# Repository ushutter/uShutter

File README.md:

# uShutter

Introduction video on Youtube:

uShutter is an open, reproducible shutter timing specification and implementation, focused on time-domain shutter speed and curtain travel measurement.

uShutter provides a firmware and multiple reference hardware interface implementation for measuring:
* shutter exposure time and stability
* curtain travel time and stability

It uses pure time-domain signals from different optical sensors. Measurement accuracy highly depends on the sensors selected and PCB board manufacturing quality.

## What uShutter Is
* An open measurement core for shutter timing
* A reference implementation for single- and dual-sensor setups
* A stable timing interface others can implement or extend
* Suitable for DIY, education, analysis, and experimentation

## Core Capabilities (Open Scope)
uShutter includes the following open-source capabilities:
### Shutter Timing
* Optical trigger–based event capture
* Microsecond-resolution timestamps
* Direction-independent logic
### Single-Sensor Measurement
* Exposure duration measurement
* Multi-shot repeatability analysis
### Dual-Sensor Curtain Analysis
* Curtain travel time
* Relative curtain speed

## Hardware Philosophy
uShutter is designed to work with:
* Arduino / ATmega328P MCUs
* Simple optical sensors (e.g. LM393-based comparators)
* No specific sensor type, threshold method, or light source is assumed by the interface.

## Project Structure
/Firmware    Code implementation 

/Hardware    Reference schematics and layouts

[Theory, usage, and build notes](https://ushutter90.wordpress.com/how-to/)

## License
Firmware: Apache License 2.0

Hardware designs: CERN-OHL-S

This project is open by design and intent.

## Status
uShutter is under active development.

Interface stability and clarity take priority over feature expansion.

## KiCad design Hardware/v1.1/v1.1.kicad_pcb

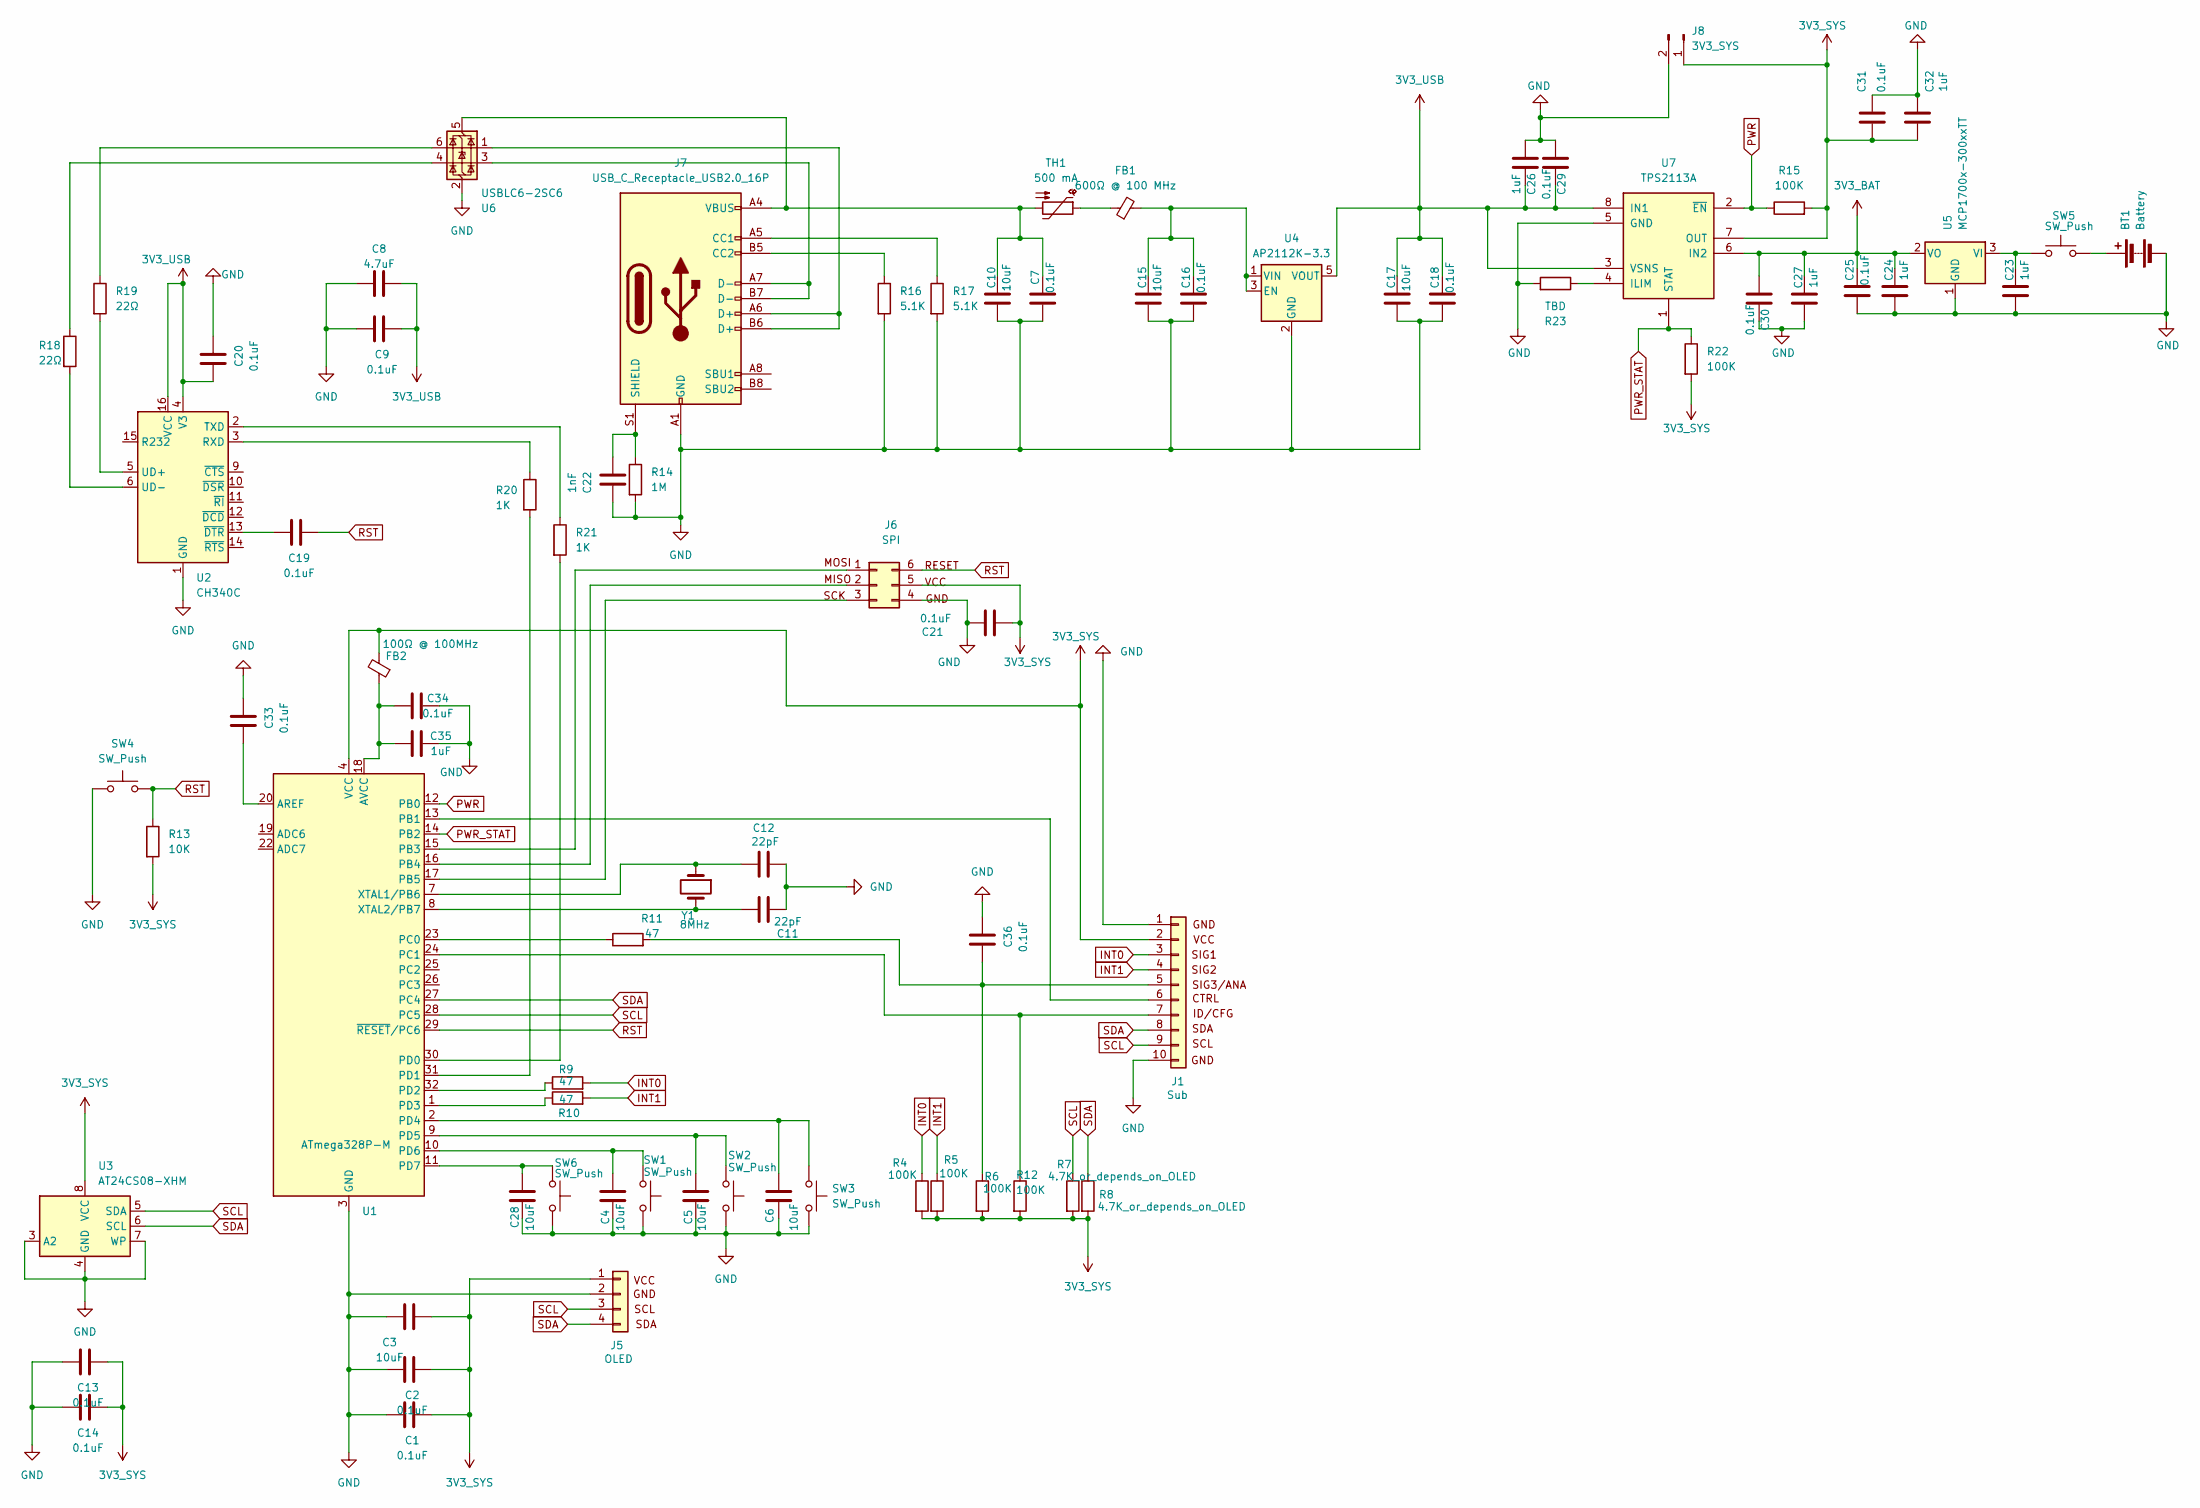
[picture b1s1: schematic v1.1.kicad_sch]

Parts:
BT1: Battery; PinHeader_1x02_P2.54mm_Vertical
C1, C2, C7, C9, C13, C14, C16, C18, C19, C20, C21, C25, C29, C30, C31, C33, C34, C36: 0.1uF; C_0603_1608Metric
C3, C4, C5, C6, C10, C15, C17, C28: 10uF; C_0805_2012Metric
C8: 4.7uF; C_0603_1608Metric
C11, C12: 22pF; C_0603_1608Metric
C22: 1nF; C_0603_1608Metric
C23, C24, C26, C27, C32, C35: 1uF; C_0603_1608Metric
FB1: 600Ω @ 100 MHz; L_0603_1608Metric
FB2: 100Ω @ 100MHz; L_0603_1608Metric
J1: Sub; PinSocket_2x05_P2.54mm_Vertical
J5: OLED; PinSocket_1x04_P2.54mm_Vertical
J6: SPI; PinSocket_2x03_P2.54mm_Vertical
J7: USB_C_Receptacle_USB2.0_16P; USB_C_Receptacle_Palconn_UTC16-G
J8: 3V3_SYS; PinHeader_1x02_P2.54mm_Vertical
R4, R5, R6, R12, R15, R22: 100K; R_0603_1608Metric
R7, R8: 4.7K_or_depends_on_OLED; R_0603_1608Metric
R9, R10, R11: 47; R_0603_1608Metric
R13: 10K; R_0603_1608Metric
R14: 1M; R_0603_1608Metric
R16, R17: 5.1K; R_0603_1608Metric
R18, R19: 22Ω; R_0603_1608Metric
R20, R21: 1K; R_0603_1608Metric
R23: TBD; R_0603_1608Metric
SW1, SW2, SW3, SW6: SW_Push; SW_PUSH_6mm
SW4, SW5: SW_Push; PinHeader_1x02_P2.54mm_Vertical
TH1: 500 mA; Fuse_1206_3216Metric
U1: ATmega328P-M; TQFP-32_7x7mm_P0.8mm
U2: CH340C; SOP-16_4.4x10.4mm_P1.27mm
U3: AT24CS08-XHM; TSSOP-8_4.4x3mm_P0.65mm
U4: AP2112K-3.3; SOT-23-5
U5: MCP1700x-300xxTT; SOT-23
U6: USBLC6-2SC6; SOT-23-6
U7: TPS2113A; TSSOP-8_4.4x3mm_P0.65mm
Y1: 8MHz; Crystal_SMD_5032-2Pin_5.0x3.2mm

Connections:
3V3_BAT: C24.2, C25.2, C27.2, C30.1, U5.2 (VO), U7.6 (IN2)
3V3_SYS: C1.2, C2.2, C3.2, C13.2, C14.2, C21.1, C31.2, C32.1, FB2.2, J1.2, J5.1, J6.5, J8.1, R4.2, R5.2, R6.2, R7.2, R8.2, R12.2, R13.2, R15.2, R22.2, U1.4 (VCC), U1.6 (VCC), U3.8 (VCC), U7.7 (OUT)
3V3_USB: C8.2, C9.2, C17.2, C18.2, C20.1, C26.2, C29.2, U2.4 (V3), U2.16 (VCC), U4.5 (VOUT), U7.3 (VSNS), U7.8 (IN1)
GND: BT1.2 (-), C1.1, C2.1, C3.1, C4.2, C5.2, C6.2, C7.1, C8.1, C9.1, C10.1, C11.2, C12.2, C13.1, C14.1, C15.1, C16.1, C17.1, C18.1, C20.2, C21.2, C22.2, C23.1, C24.1, C25.1, C26.1, C27.1, C28.2, C29.1, C30.2, C31.1, C32.2, C33.2, C34.2, C35.2, C36.2, J1.1, J1.10, J5.2, J6.4, J7.A1 (GND), J7.A12 (GND), J7.B1 (GND), J7.B12 (GND), J8.2, R14.2, R16.2, R17.2, R23.2, SW1.2, SW2.2, SW3.2, SW4.1, SW6.2, U1.3 (GND), U1.5 (GND), U1.21 (GND), U1.33 (GND), U2.1 (GND), U3.3 (A2), U3.4 (GND), U3.7 (WP), U4.2 (GND), U5.1 (GND), U6.2 (GND), U7.5 (GND)
INT0: J1.3, R4.1, R9.2
INT1: J1.4, R5.1, R10.2
unnamed: BT1.1 (+), SW5.2
unnamed: FB1.1, TH1.1
unnamed: C36.1, J1.5, R6.1, R11.2
unnamed: J1.6, U1.13 (PB1)
unnamed: J1.7, R12.1, U1.24 (PC1)
unnamed: J6.1, U1.15 (PB3)
unnamed: J6.2, U1.16 (PB4)
unnamed: J6.3, U1.17 (PB5)
unnamed: J7.A5 (CC1), R17.1
unnamed: J7.B5 (CC2), R16.1
unnamed: J7.A6 (D+), J7.B6 (D+), U6.1 (I/O1)
unnamed: J7.A7 (D-), J7.B7 (D-), U6.3 (I/O2)
unnamed: C22.1, J7.S1 (SHIELD), R14.1
unnamed: R18.1, U6.4 (I/O2)
unnamed: R19.1, U6.6 (I/O1)
unnamed: C33.1, U1.20 (AREF)
unnamed: C34.1, C35.1, FB2.1, U1.18 (AVCC)
unnamed: R11.1, U1.23 (PC0)
unnamed: R21.2, U1.30 (PD0)
unnamed: R20.2, U1.31 (PD1)
unnamed: R9.1, U1.32 (PD2)
unnamed: R10.1, U1.1 (PD3)
unnamed: C6.1, SW3.1, U1.2 (PD4)
unnamed: C5.1, SW2.1, U1.9 (PD5)
unnamed: C4.1, SW1.1, U1.10 (PD6)
unnamed: C28.1, SW6.1, U1.11 (PD7)
unnamed: C12.1, U1.7 (XTAL1/PB6), Y1.1
unnamed: C11.1, U1.8 (XTAL2/PB7), Y1.2
unnamed: R20.1, U2.3 (RXD)
unnamed: R21.1, U2.2 (TXD)
unnamed: R19.2, U2.5 (UD+)
unnamed: R18.2, U2.6 (UD-)
unnamed: C19.1, U2.13 (~DTR)
unnamed: C15.2, C16.2, FB1.2, U4.1 (VIN), U4.3 (EN)
unnamed: C23.2, SW5.1, U5.3 (VI)
unnamed: C7.2, C10.2, J7.A4 (VBUS), J7.A9 (VBUS), J7.B4 (VBUS), J7.B9 (VBUS), TH1.2, U6.5 (VBUS)
unnamed: R23.1, U7.4 (ILIM)
PWR: R15.1, U1.12 (PB0), U7.2 (~EN)
PWR_STAT: R22.1, U1.14 (PB2), U7.1 (STAT)
RST: C19.2, J6.6, R13.1, SW4.2, U1.29 (~RESET/PC6)
SCL: J1.9, J5.3, R7.1, U1.28 (PC5), U3.5 (SDA)
SDA: J1.8, J5.4, R8.1, U1.27 (PC4), U3.6 (SCL)

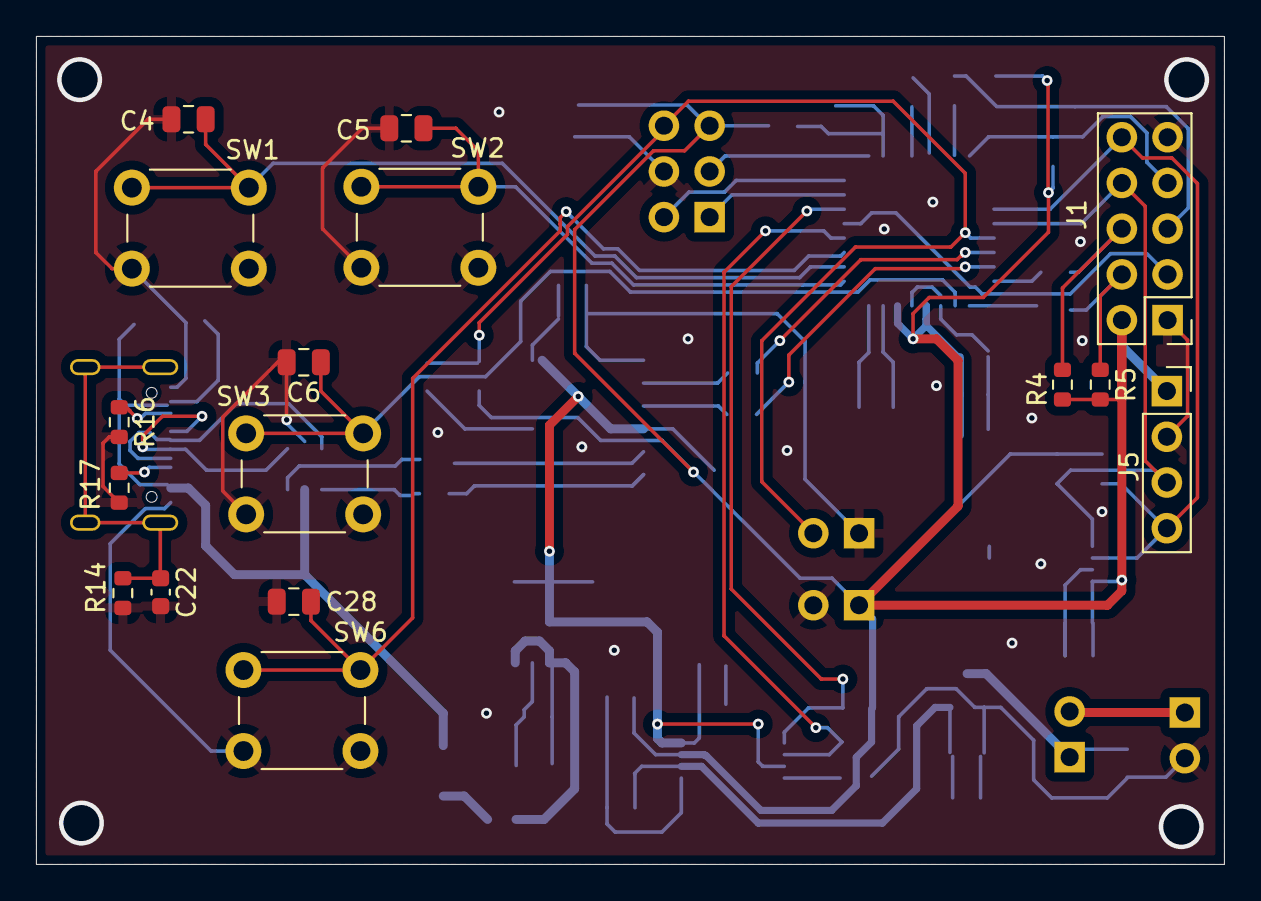
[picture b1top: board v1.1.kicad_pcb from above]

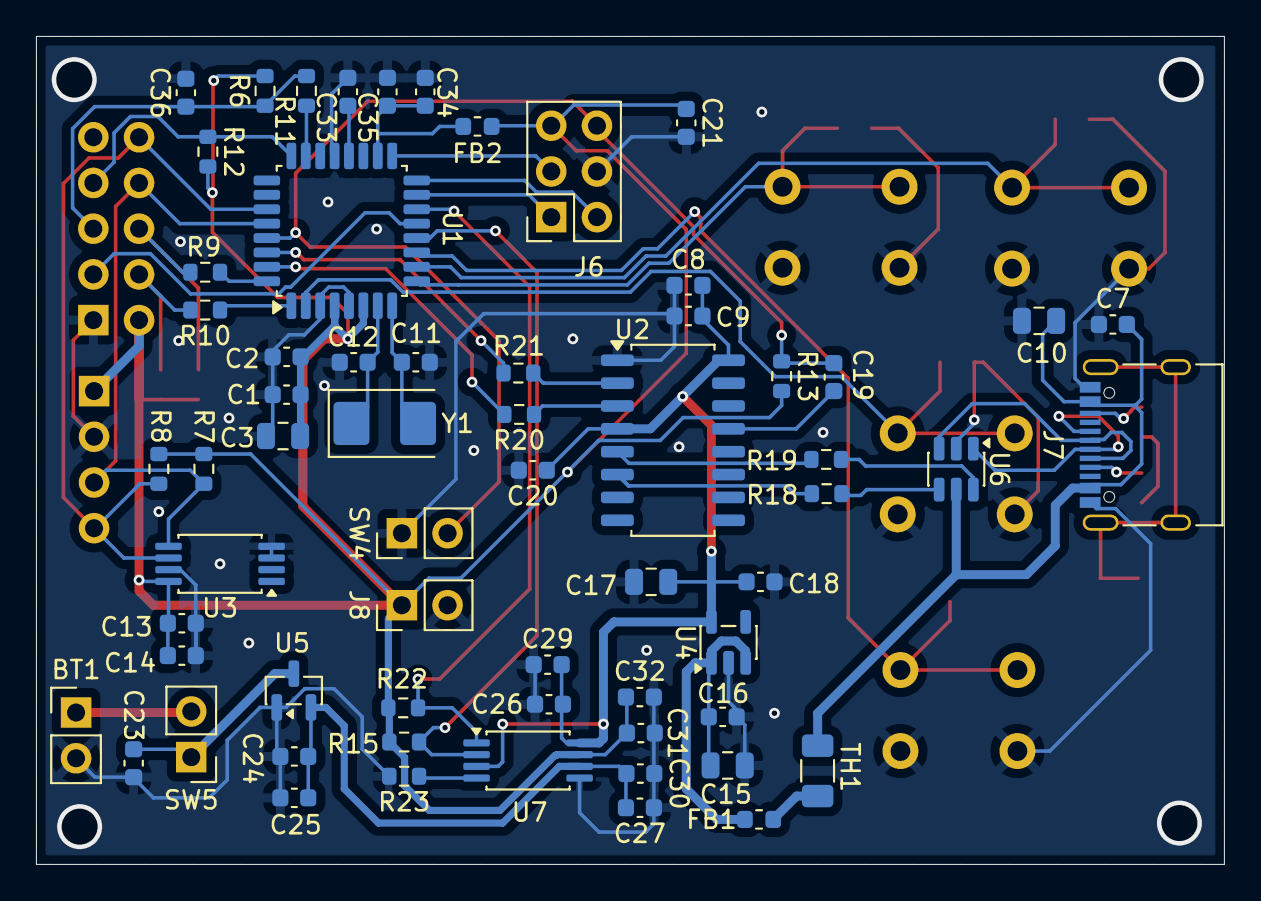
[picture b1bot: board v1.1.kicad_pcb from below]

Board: 2 copper layers, 66.0 x 46.0 mm, 79 parts (63 on the bottom side), 48 nets.

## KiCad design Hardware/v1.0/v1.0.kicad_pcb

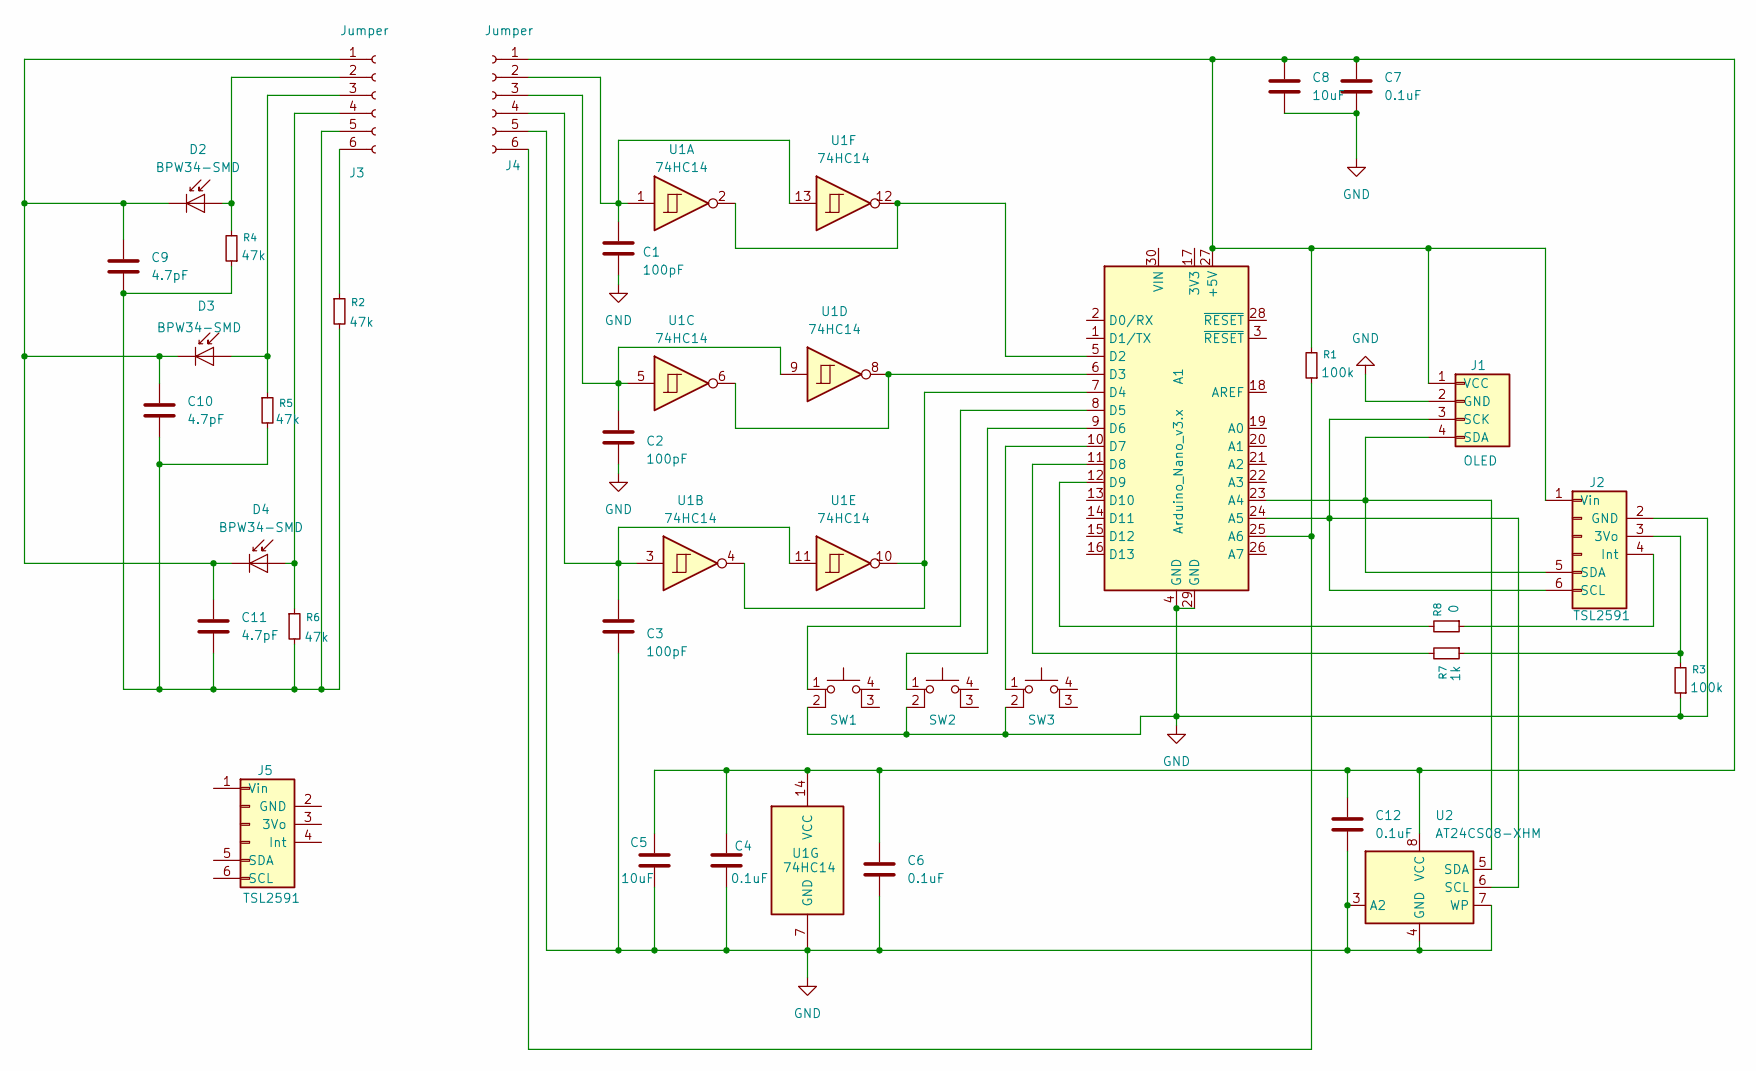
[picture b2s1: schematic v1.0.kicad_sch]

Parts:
A1: Arduino_Nano_v3.x; Arduino_Nano
C1, C2, C3: 100pF; C_0603_1608Metric
C4, C6, C7, C12: 0.1uF; C_0603_1608Metric
C5, C8: 10uF; C_0603_1608Metric
C9, C10, C11: 4.7pF; C_0603_1608Metric
D2, D3, D4: BPW34-SMD; Osram_BPW34S-SMD
J1: OLED; R_Array_SIP4
J2, J5: TSL2591; R_Array_SIP6
J3, J4: Jumper; R_Array_SIP6
R1, R3: 100k; R_0603_1608Metric
R2, R4, R5, R6: 47k; R_0603_1608Metric
R7: 1k; R_0603_1608Metric
R8: 0; R_0603_1608Metric
SW1, SW2, SW3: SW_MEC_5E; SW_PUSH_6mm
U1: 74HC14; SSOP-14_5.3x6.2mm_P0.65mm
U2: AT24CS08-XHM; TSSOP-8_4.4x3mm_P0.65mm

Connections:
GND: A1.4 (GND), A1.29 (GND), C1.2, C2.2, C3.2, C4.2, C5.2, C6.2, C7.2, C8.2, C12.2, J1.2 (GND), J2.2 (GND), J4.5, R3.1, SW1.2, SW2.2, SW3.2, U1.7 (GND), U2.3 (A2), U2.4 (GND), U2.7 (WP)
unnamed: A1.27 (+5V), C4.1, C5.1, C6.1, C7.1, C8.1, C12.1, J1.1 (VCC), J2.1 (Vin), J4.1, R1.2, U1.14 (VCC), U2.8 (VCC)
unnamed: A1.23 (A4), J1.4 (SDA), J2.5 (SDA), U2.5 (SDA)
unnamed: A1.24 (A5), J1.3 (SCK), J2.6 (SCL), U2.6 (SCL)
unnamed: A1.25 (A6), J4.6, R1.1
unnamed: A1.5 (D2), U1.2, U1.12
unnamed: A1.6 (D3), U1.6, U1.8
unnamed: A1.7 (D4), U1.4, U1.10
unnamed: A1.8 (D5), SW1.1
unnamed: A1.9 (D6), SW2.1
unnamed: A1.10 (D7), SW3.1
unnamed: A1.11 (D8), R7.2
unnamed: A1.12 (D9), R8.2
unnamed: D2.2 (A), J3.2, R4.2
unnamed: C9.1, C10.1, C11.1, D2.1 (K), D3.1 (K), D4.1 (K), J3.1
unnamed: D3.2 (A), J3.3, R5.1
unnamed: D4.2 (A), J3.4, R6.1
unnamed: J2.3 (3Vo), R3.2, R7.1
unnamed: J2.4 (Int), R8.1
unnamed: C9.2, C10.2, C11.2, J3.5, R2.2, R4.1, R5.2, R6.2
unnamed: J3.6, R2.1
unnamed: C1.1, J4.2, U1.1, U1.13
unnamed: C2.1, J4.3, U1.5, U1.9
unnamed: C3.1, J4.4, U1.3, U1.11

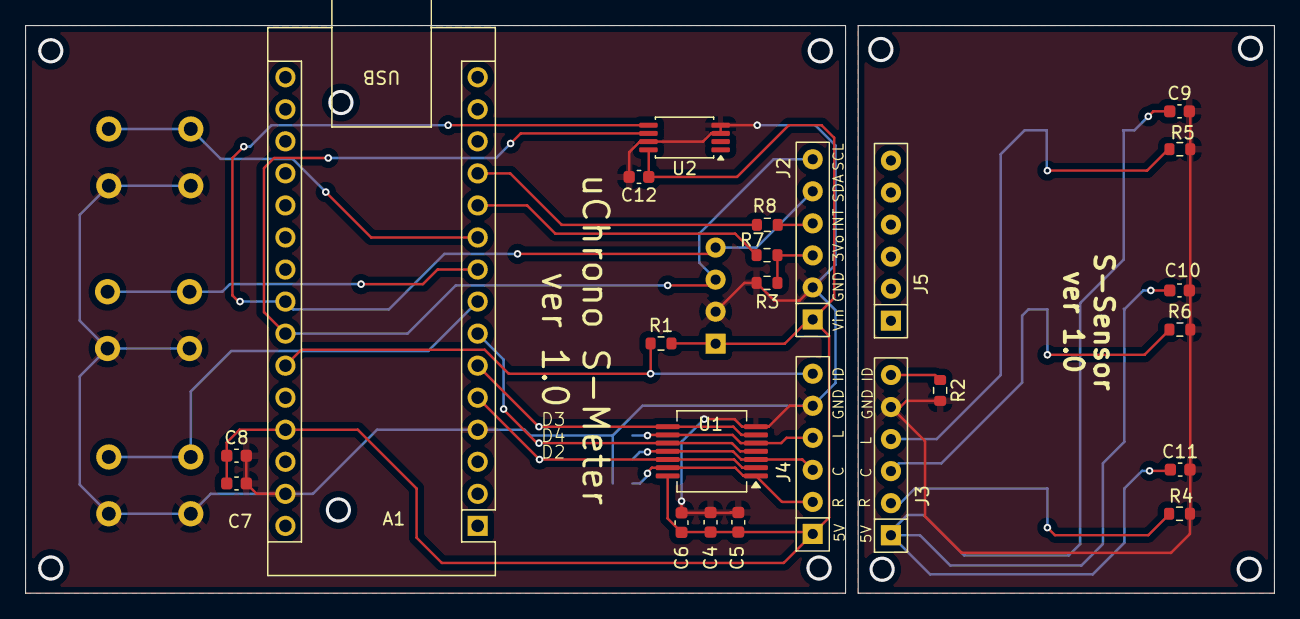
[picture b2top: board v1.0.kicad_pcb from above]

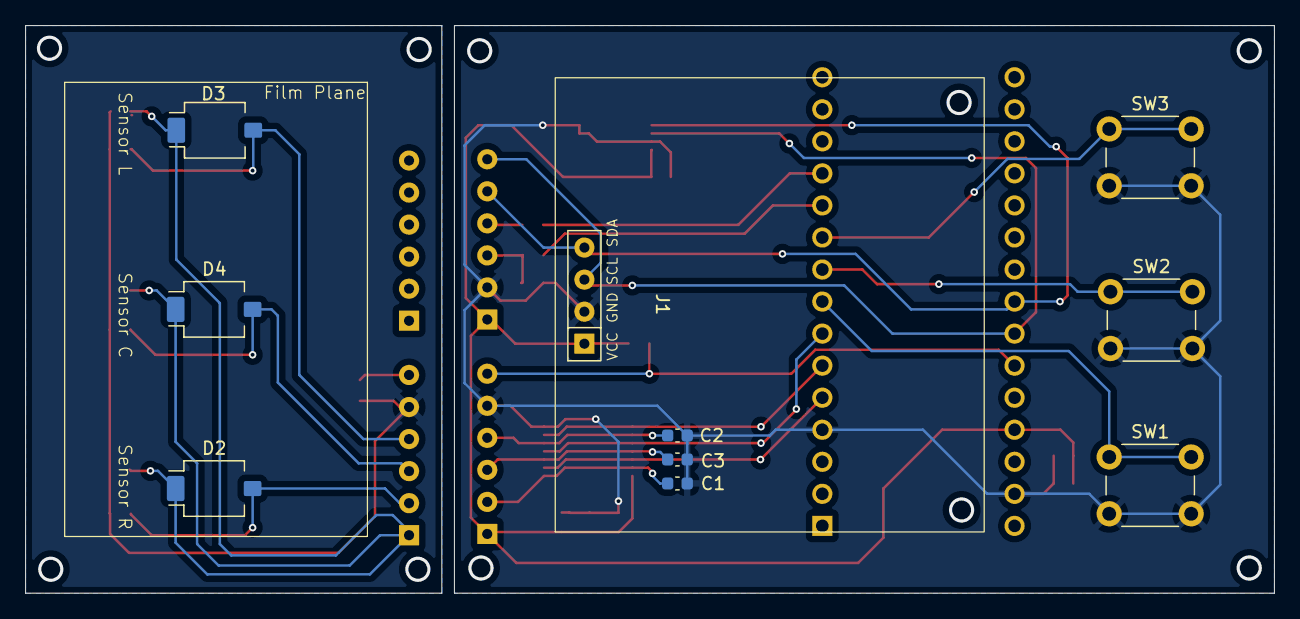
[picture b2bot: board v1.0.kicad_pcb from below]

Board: 2 copper layers, 99.0 x 45.0 mm, 34 parts (10 on the bottom side), 24 nets.

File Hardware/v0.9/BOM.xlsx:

Id | 类型 | 型号 | 封装 |  | 数量
1 | U1 | 74HC14 SSOP | SSOP-14_5.3x6.2mm_P0.65mm | 1 | 6
2 | U2 | AT24CS16-XHM TSSOP | TSSOP-8_4.4x3mm_P0.65mm | 1 | 6
3 | D2,D3,D4 | VISHAY_BPW34S | SMD | 3 | 18
4 | SW3,SW1,SW2 | 开关 | SW_PUSH_6mm | 3 | 18
5 | J1 | 1x4孔排针插座2.54mm | SIP4 | 1 | 6
6 | J3 | 1x6孔90度排针2.54mm | SIP6 | 2 | 12
7 | J2,J5 | 1x6孔排针插座2.54mm | SIP6 | 2 | 12
8 | J4 | 1x10孔排针插座2.54mm | SIP10 | 2 | 12
9 | R3,R1 | 100k | R_0603_1608Metric | 2 | 40
10 | R5,R2,R6,R4 | 47k | R_0603_1608Metric | 4 | 80
11 | R7 | 1k | R_0603_1608Metric | 1 | 20
12 | C3,C1,C2 | 100pF | C_0603_1608Metric | 3 | 60
13 | C5,C8 | 10uF | C_0603_1608Metric | 2 | 40
14 | C4,C12,C7,C6 | 0.1uF | C_0603_1608Metric | 4 | 80
15 | C11,C9,C10 | 4.7pF | C_0603_1608Metric | 3 | 60
16 | PCB安装螺丝 |  | 2mm | 10 | 50
17 | 其他电阻电容 |  | C_0603_1608Metric |  | 若干

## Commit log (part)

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2026-02-05 init
2026-02-05 remove hardware
2026-02-05 Format README.md with Markdown syntax
2026-02-05 setup
2026-02-05 update HW
2026-02-05 update readme and license
2026-02-05 Fix README formatting and update links
    Corrected capitalization and updated documentation links.
2026-02-08 release v0.9.2
2026-02-26 update code according to v1.0.3 hardware, functionalies are equivalent to v0.9.2 code. 1. Add 74AHC14 display 2. adjust ID/CFG resistor and adc value, 3. allow user to select sensor for single mode
2026-02-26 add all
2026-02-26 Revert "add all"
    This reverts commit acbe82ba5c7bee5f6fd0c139b5e62855f1dc90a6.
2026-02-26 latest
2026-03-08 Move uShutter sketch from Firmware/v0.9.4 to Firmware root
2026-03-08 Refactor Firmware sketch into modular app/display/capture files
2026-03-08 Refactor README to update file name
    Renamed the main Arduino file for clarity.
2026-03-08 Add Hardware 1.0.3 files
2026-03-23 Rename main sketch to UShutter.ino
2026-03-23 Add firmware v0.9.6 and rename sketch to uShutter.ino
2026-03-23 Move v0.9.6 files to Firmware root (remove nested folder)
2026-03-23 Use v0.9.6 log as Firmware/Changes_log.md (remove duplicate filename)
2026-04-02 Sync Firmware from Documents/uShutter_v0_9_7
2026-04-02 Preserve existing Firmware/v0.9.2 legacy file
2026-04-02 Add Firmware/v0.9.7 folder and sync v0.9.7 files to Firmware root
